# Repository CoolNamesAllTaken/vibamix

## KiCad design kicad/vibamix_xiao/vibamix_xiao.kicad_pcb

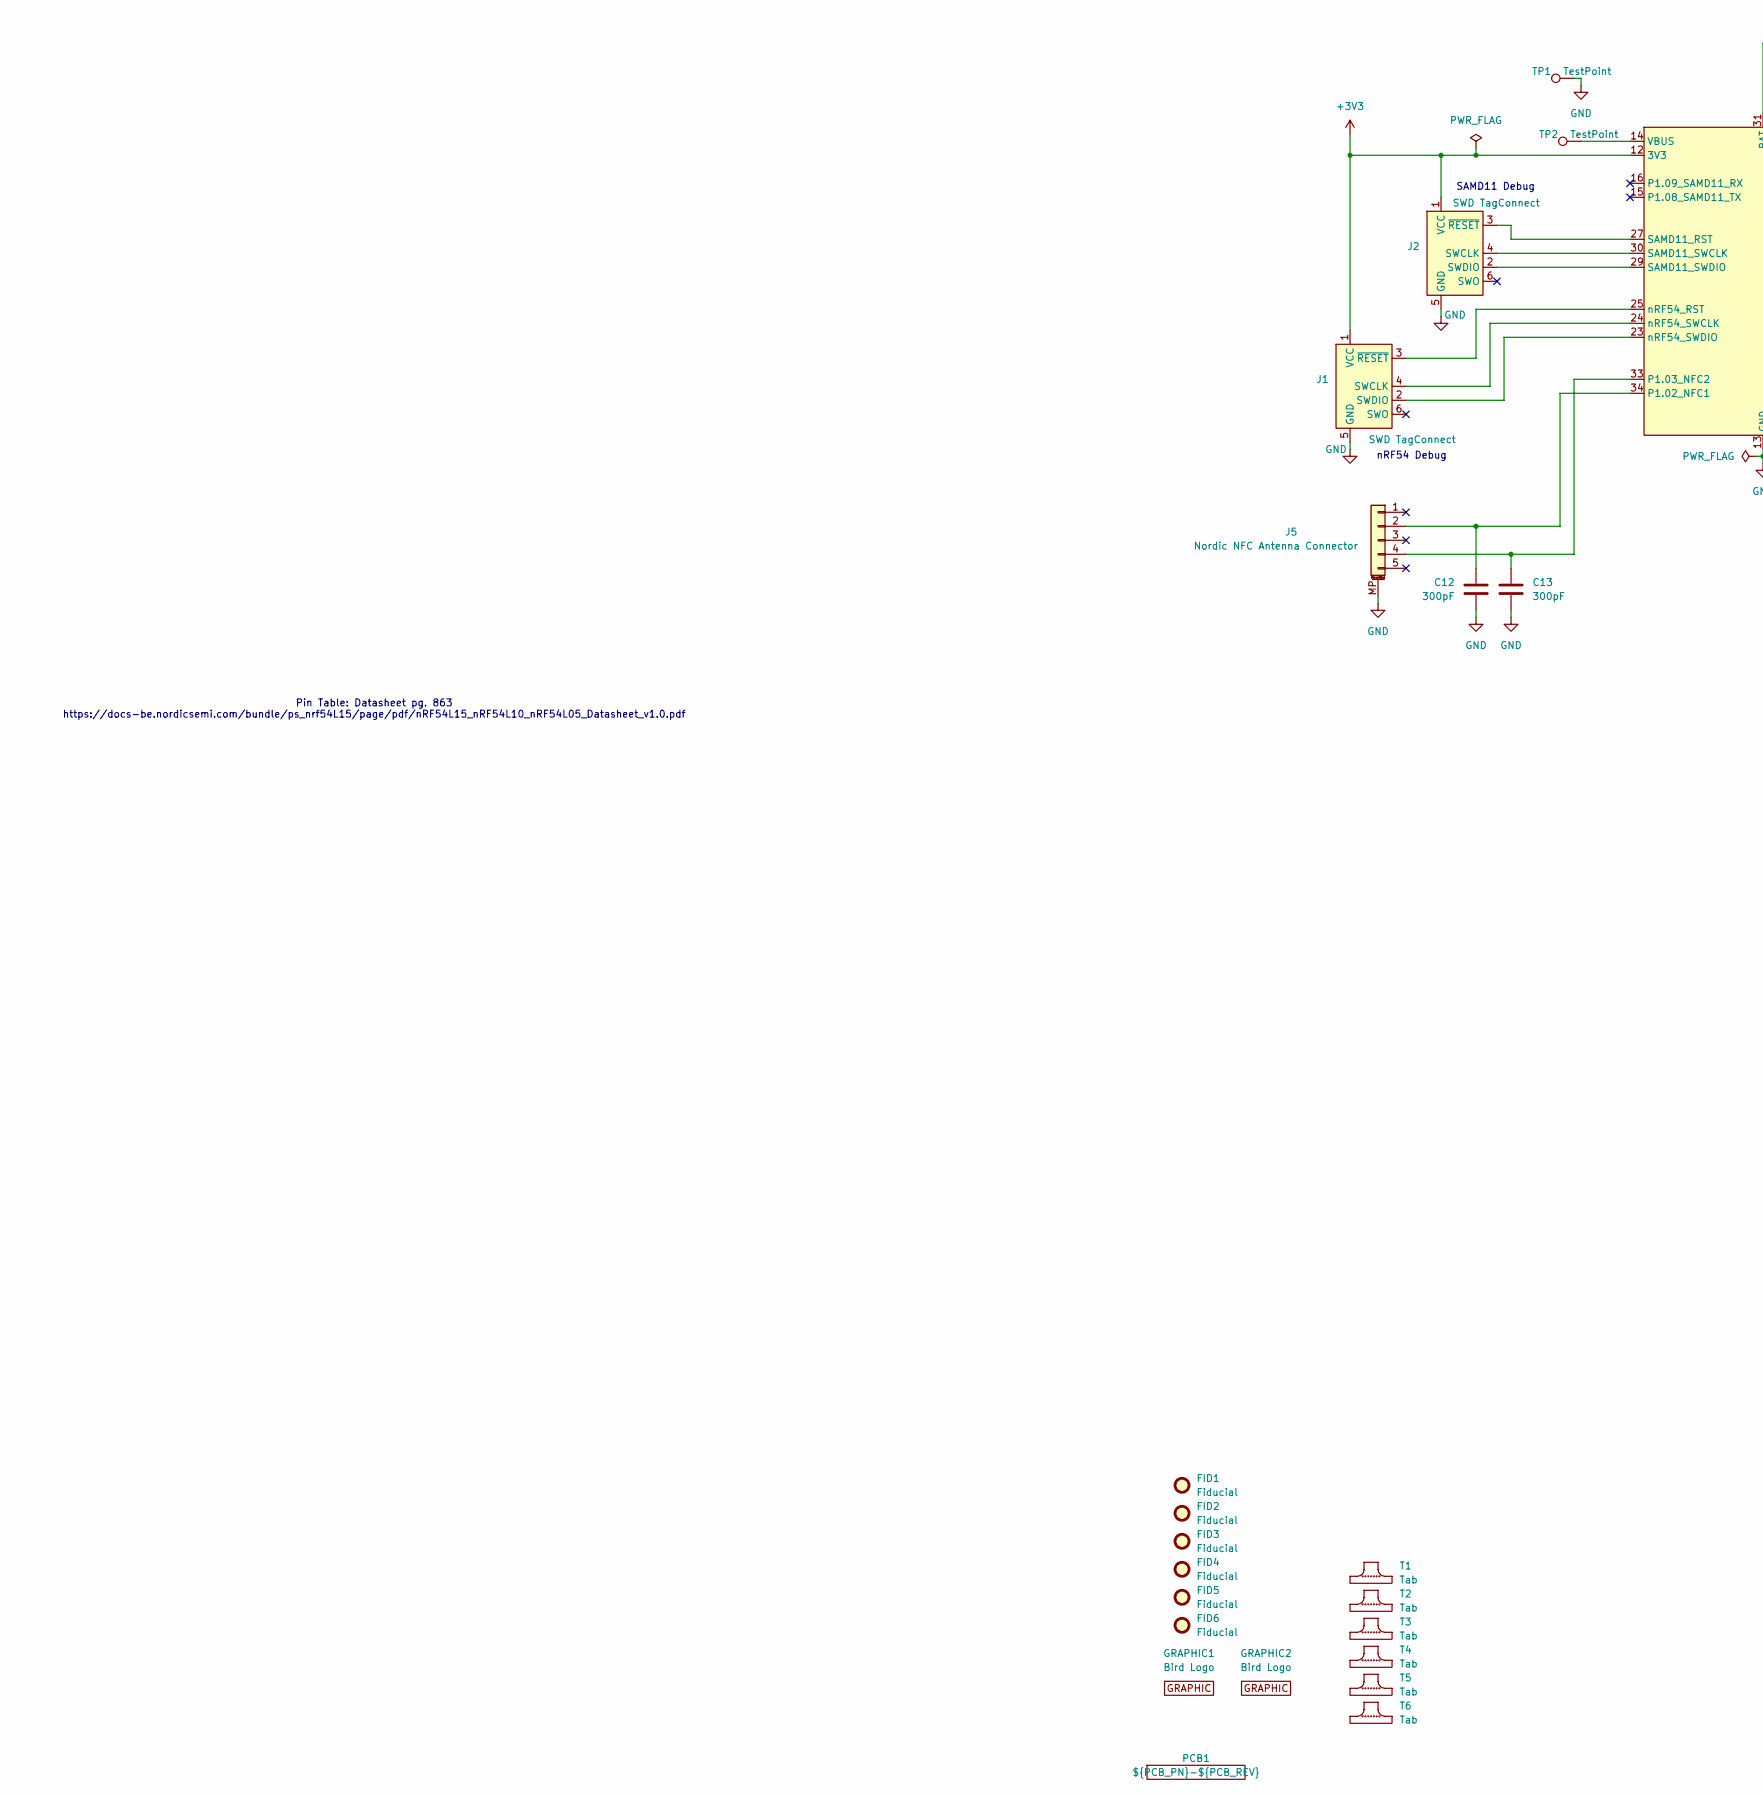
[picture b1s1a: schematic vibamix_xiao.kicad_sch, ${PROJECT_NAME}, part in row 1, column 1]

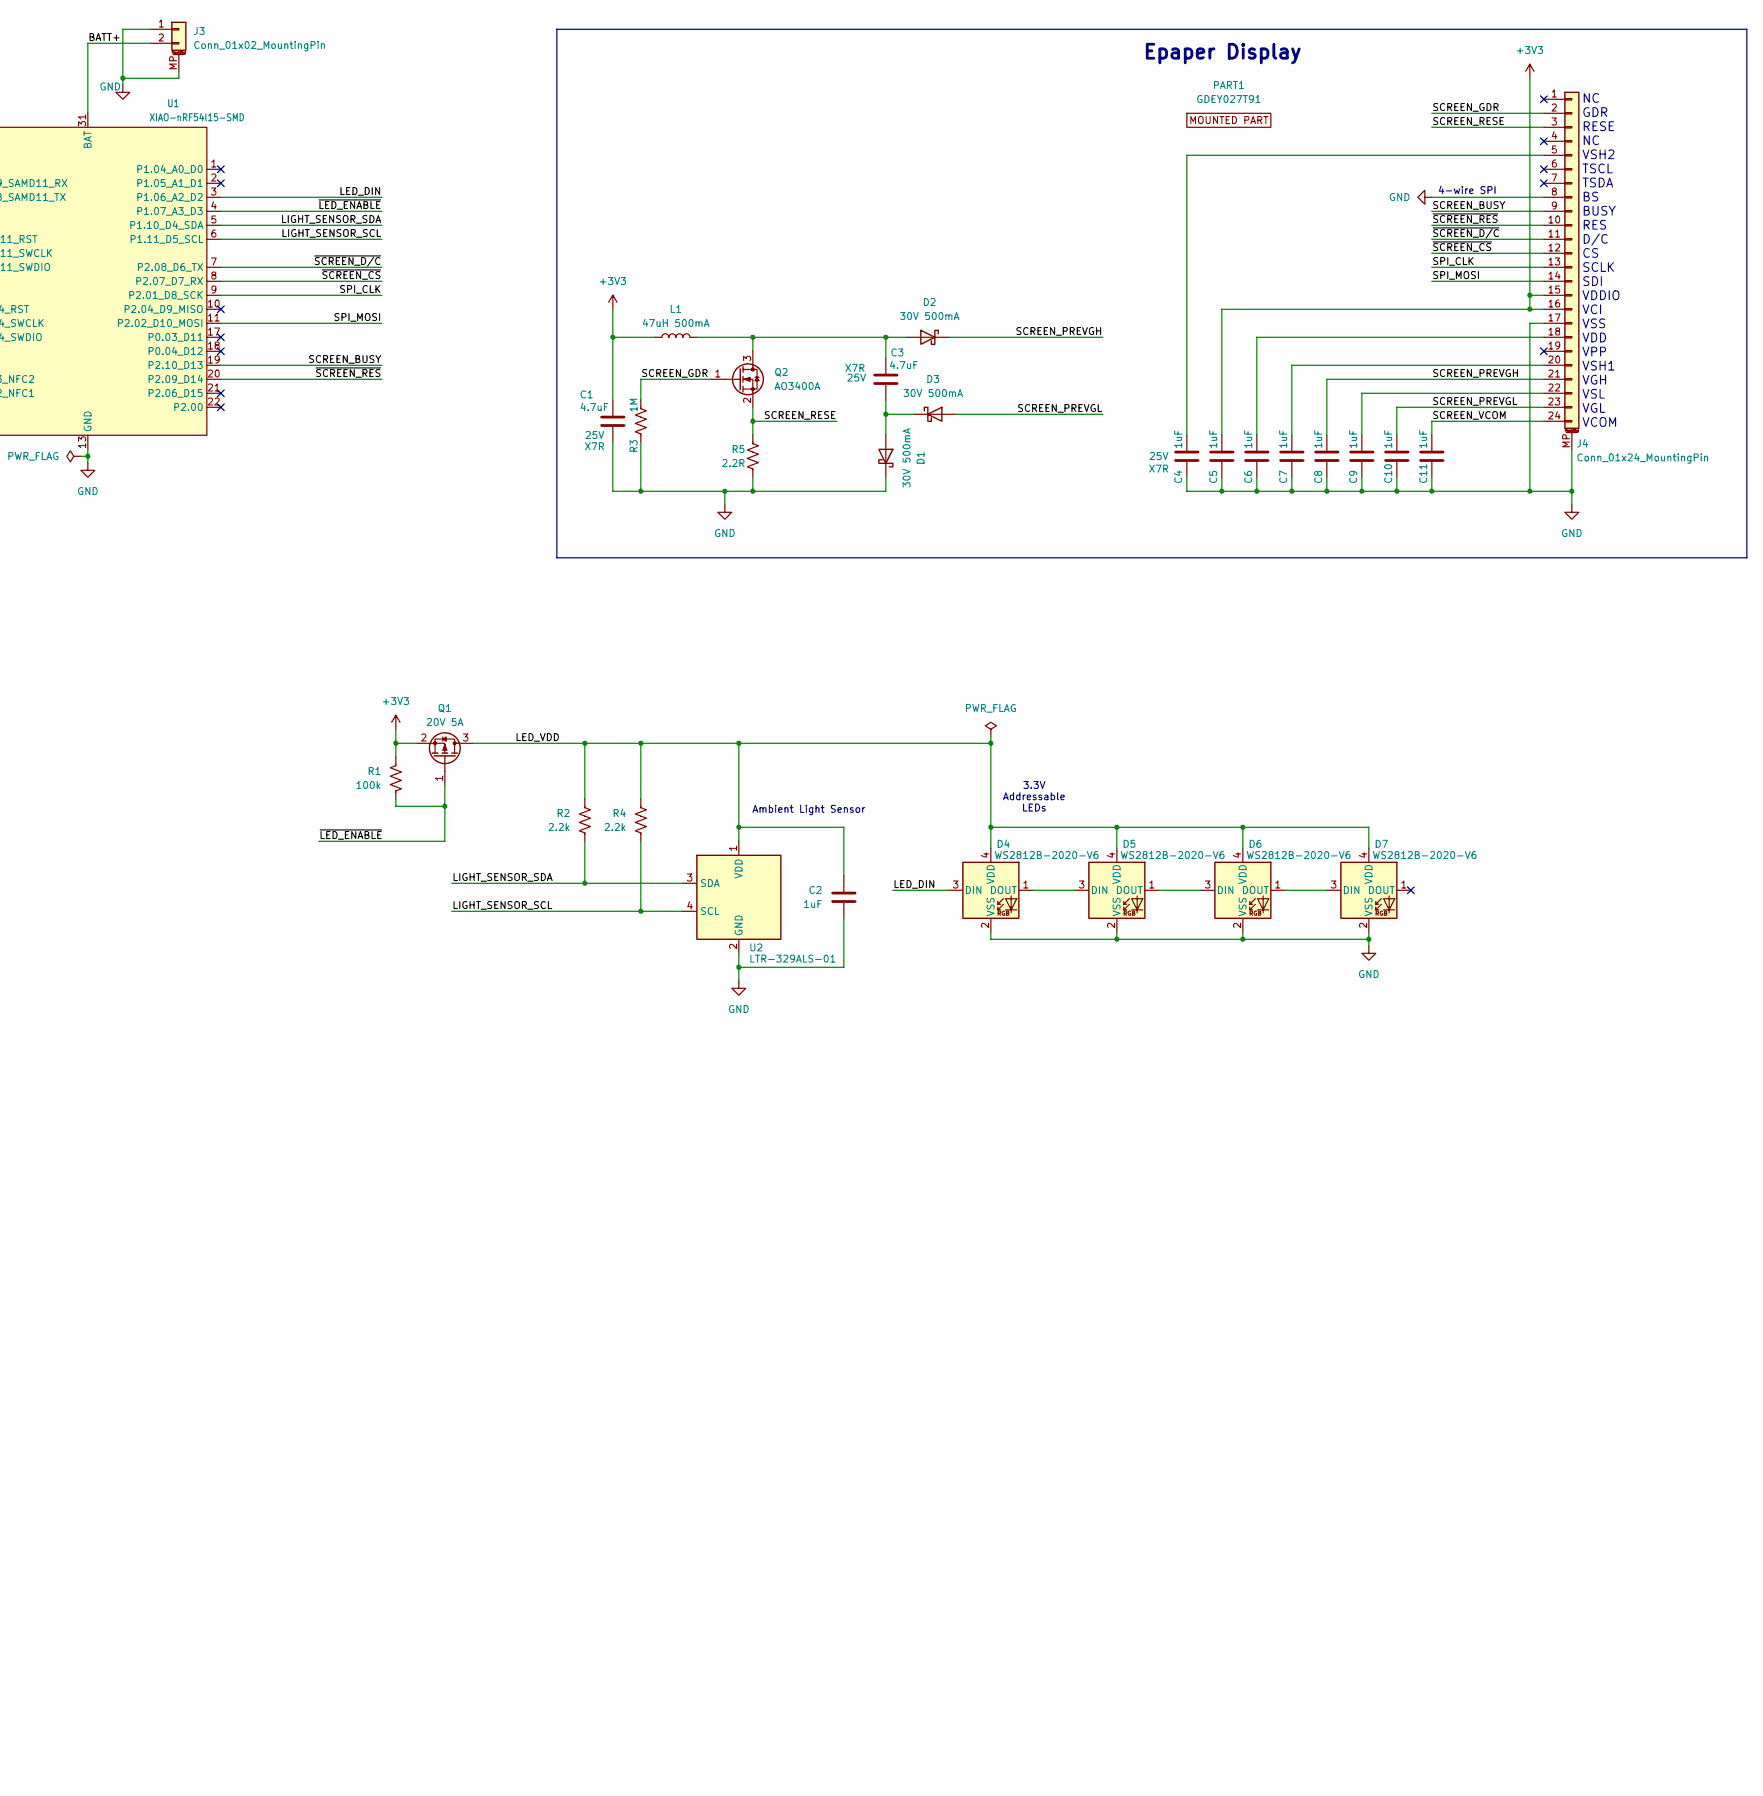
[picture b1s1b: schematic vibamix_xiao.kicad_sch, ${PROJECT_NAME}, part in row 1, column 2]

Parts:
C1, C3: 4.7uF; C_0805_2012Metric; Voltage 25V; Tolerance 10%; MPN CL21B475KAFNNNE; LCSC PN C98195
C2, C4, C5, C6, C7, C8, C9, C10, C11: 1uF; C_0603_1608Metric; Voltage 25V; MPN CL10B105KA8NNNC; LCSC PN C29936
C12, C13: 300pF; C_0402_1005Metric; MPN GRM1555C1H301JA01D
D1, D2, D3: 30V 500mA; D_SOD-123; MPN B0530W-7-F; LCSC PN C124188
D4, D5, D6, D7: WS2812B-2020-V6; LED_WS2812B-2020_PLCC4_2.0x2.0mm; MPN WS2812B-2020-V6; LCSC PN C52917434
FID1, FID2, FID3, FID4, FID5, FID6: Fiducial; Fiducial_0.5mm_Mask1mm_NoCourtyard
GRAPHIC1: Bird Logo; BirdWithPants_Small_Left
GRAPHIC2: Bird Logo; BirdWithPants_Small_Right
J1, J2: SWD TagConnect; Tag-Connect_TC2030-IDC-NL_2x03_P1.27mm_Vertical
J3: Conn_01x02_MountingPin; Molex_PicoBlade_53261-0271_1x02-1MP_P1.25mm_Horizontal; MPN 0532610271
J4: Conn_01x24_MountingPin; Hirose_FH34SRJ-24S-0.5SH_1x24-1MP_P0.50mm_Horizontal_Mirror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; MPN FH34SRJ-24S-0.5SH(50)
J5: Nordic NFC Antenna Connector; FPC-SMD_5P-P0.50_HCTL_HC-FPC-05-10-5RLTAG; MPN HC-FPC-05-10-5RLTAG
L1: 47uH 500mA; L_APV_ANR4012; MPN ANR4012T470M; LCSC PN C7497063
PART1: GDEY027T91; GDEY027T91_NoSlot; MPN GDEY027T91
PCB1: ${PCB_PN}-${PCB_REV}; PCB_PN_REV_Tiny_Silkscreen; MPN ${PCB_PN}
Q1: 20V 5A; SOT-23; MPN DMG2305UX-7
Q2: AO3400A; SOT-23; MPN AO3400A
R1: 100k; R_0402_1005Metric; MPN RC0402FR-07100KL
R2, R4: 2.2k; R_0402_1005Metric; MPN RC0402FR-072K2L
R3: 1M; R_0402_1005Metric; Tolerance 1%; MPN RC0402FR-071ML; LCSC PN C138033
R5: 2.2R; R_0603_1608Metric; Tolerance 1%; MPN RC0603FR-072R2L; LCSC PN C112307
T1, T2, T3, T4, T5, T6: Tab
TP1, TP2: TestPoint; TestPoint_Pad_D1.0mm
U1: XIAO-nRF54l15-SMD; MPN XIAO-nRF54l15-SMD
U2: LTR-329ALS-01; Lite-On_LTR-329ALS-01; MPN LTR-329ALS-01

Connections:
+3V3: C1.2, C5.1, J1.1 (VCC), J2.1 (VCC), J4.15, J4.16, L1.1, Q1.2 (S), R1.1, U1.12 (3V3), U1.28 (3V3)
/BATT+: J3.2, U1.31 (BAT)
/LED_DIN: D4.3 (DIN), U1.3 (P1.06_A2_D2)
/LED_VDD: C2.1, D4.4 (VDD), D5.4 (VDD), D6.4 (VDD), D7.4 (VDD), Q1.3 (D), R2.1, R4.1, U2.1 (VDD)
/LIGHT_SENSOR_SCL: R4.2, U1.6 (P1.11_D5_SCL), U2.4 (SCL)
/LIGHT_SENSOR_SDA: R2.2, U1.5 (P1.10_D4_SDA), U2.3 (SDA)
/SCREEN_BUSY: J4.9, U1.19 (P2.10_D13)
/SCREEN_GDR: J4.2, Q2.1 (G), R3.2
/SCREEN_PREVGH: C8.1, D2.1 (K), J4.21
/SCREEN_PREVGL: C10.1, D3.2 (A), J4.23
/SCREEN_RESE: J4.3, Q2.2 (S), R5.1
/SCREEN_VCOM: C11.1, J4.24
/SPI_CLK: J4.13, U1.9 (P2.01_D8_SCK)
/SPI_MOSI: J4.14, U1.11 (P2.02_D10_MOSI)
/~LED_ENABLE: Q1.1 (G), R1.2, U1.4 (P1.07_A3_D3)
/~SCREEN_CS: J4.12, U1.8 (P2.07_D7_RX)
/~SCREEN_D/C: J4.11, U1.7 (P2.08_D6_TX)
/~SCREEN_RES: J4.10, U1.20 (P2.09_D14)
GND: C1.1, C2.2, C4.2, C5.2, C6.2, C7.2, C8.2, C9.2, C10.2, C11.2, C12.2, C13.2, D1.1 (K), D4.2 (VSS), D5.2 (VSS), D6.2 (VSS), D7.2 (VSS), J1.5 (GND), J2.5 (GND), J3.1, J3.MP (MountPin), J4.8, J4.17, J4.MP (MountPin), J5.MP (MountPin), R3.1, R5.2, TP1.1 (1_1), U1.13 (GND), U1.26 (GND), U1.32 (GND), U2.2 (GND)
unnamed: C3.1, D1.2 (A), D3.1 (K)
unnamed: C3.2, D2.2 (A), L1.2, Q2.3 (D)
unnamed: D4.1 (DOUT), D5.3 (DIN)
unnamed: D5.1 (DOUT), D6.3 (DIN)
unnamed: D6.1 (DOUT), D7.3 (DIN)
unnamed: J1.4 (SWCLK), U1.24 (nRF54_SWCLK)
unnamed: J1.2 (SWDIO), U1.23 (nRF54_SWDIO)
unnamed: J1.3 (~RESET), U1.25 (nRF54_RST)
unnamed: J2.4 (SWCLK), U1.30 (SAMD11_SWCLK)
unnamed: J2.2 (SWDIO), U1.29 (SAMD11_SWDIO)
unnamed: J2.3 (~RESET), U1.27 (SAMD11_RST)
unnamed: C4.1, J4.5
unnamed: C6.1, J4.18
unnamed: C7.1, J4.20
unnamed: C9.1, J4.22
unnamed: C12.1, J5.2, U1.34 (P1.02_NFC1)
unnamed: C13.1, J5.4, U1.33 (P1.03_NFC2)
unnamed: TP2.1 (1_1), U1.14 (VBUS)

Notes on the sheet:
SAMD11 Debug
Ambient Light Sensor
NC GDR RESE NC VSH2 TSCL TSDA BS BUSY RES D/C CS SCLK SDI VDDIO VCI VSS VDD VPP VSH1 VGH VSL VGL VCOM
Pin Table: Datasheet pg. 863 https://docs-be.nordicsemi.com/bundle/ps_nrf54L15/page/pdf/nRF54L15_nRF54L10_nRF54L05_Datasheet_v1.0.pdf
Epaper Display
4-wire SPI
nRF54 Debug
3.3V Addressable LEDs

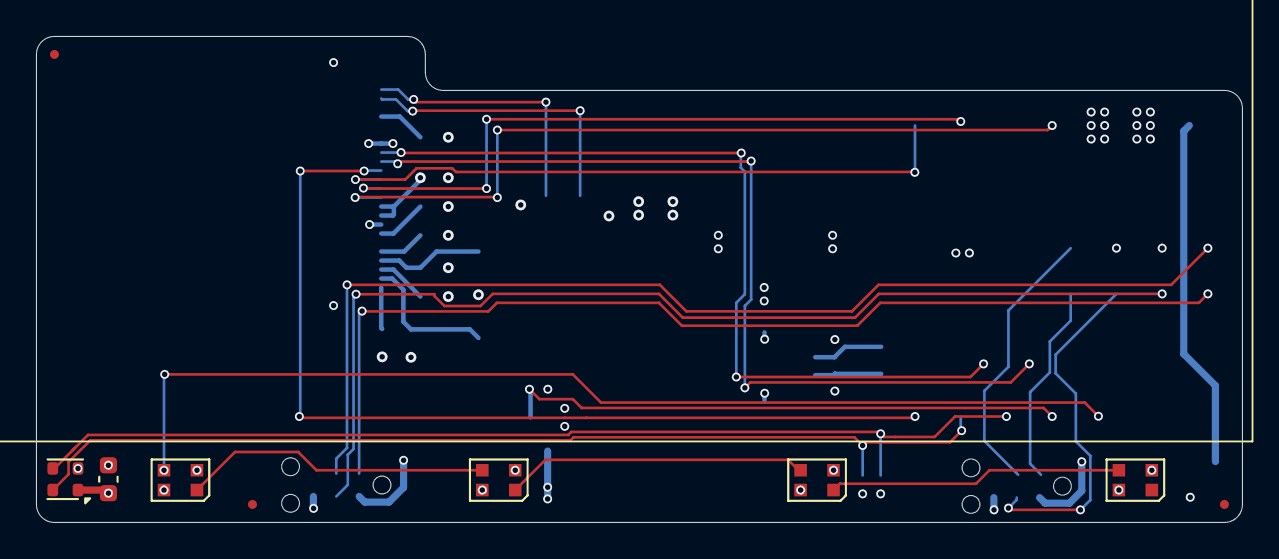
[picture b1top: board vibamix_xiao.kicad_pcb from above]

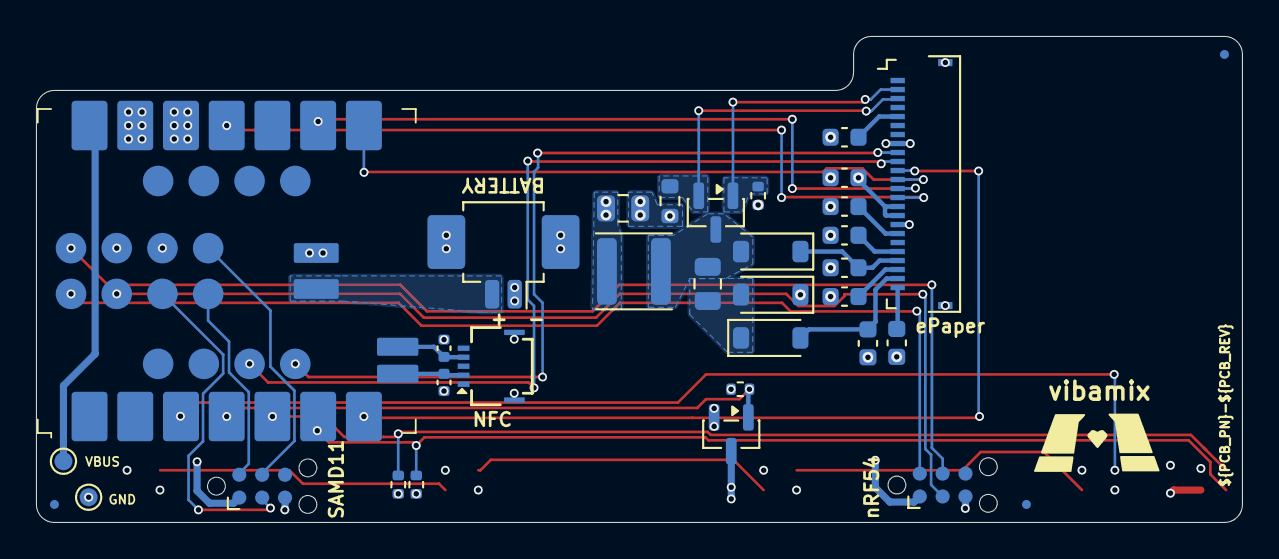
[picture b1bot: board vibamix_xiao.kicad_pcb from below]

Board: 4 copper layers, 67.0 x 27.0 mm, 53 parts (37 on the bottom side), 37 nets.

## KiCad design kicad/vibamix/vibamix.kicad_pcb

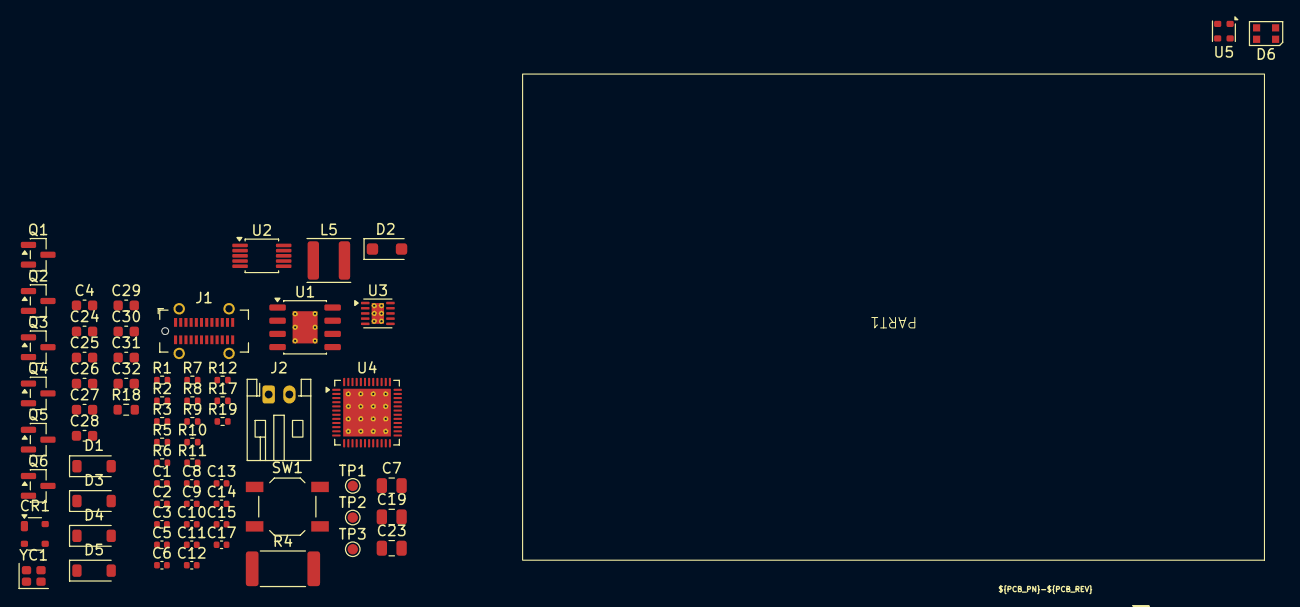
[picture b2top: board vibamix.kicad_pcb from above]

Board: 4 copper layers, 78 parts (1 on the bottom side), 35 nets, no tracks yet.

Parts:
C1, C2, C5, C8, C9, C10, C11, C13: 10uF; C_0402_1005Metric
C3, C6, C12, C14, C15, C17: 0.1uF; C_0402_1005Metric
C4, C24, C25, C26, C27, C28, C29, C30, C31, C32: 1uF; C_0603_1608Metric
C7: 10uF; C_0805_2012Metric
C19, C23: 4.7uF; C_0805_2012Metric
CR1: DRTR5V0U2SR-7; SOT-143
D1: 1N4148; D_SOD-123
D2: 40V 2A; D_SOD-123F
D3, D4, D5: 30V 500mA; D_SOD-123
D6: WS2812B-2020-V6; LED_WS2812B-2020_PLCC4_2.0x2.0mm
GRAPHIC1: Bird Logo; BirdWithPants_Small_Left
H1, H2: M2.5 Mounting Hole; MountingHole_2.7mm_M2.5_Isolated
J1: USB_C_Receptacle_USB2.0; USB_C_Receptacle_GCT_USB4115-03-C
J2: JST-PH 01x02 Male; JST_PH_S2B-PH-K_1x02_P2.00mm_Horizontal
J4: Conn_01x24_MountingPin; Hirose_FH34SRJ-24S-0.5SH_1x24-1MP_P0.50mm_Horizontal_Mirror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
L5: 47uH 500mA; L_APV_ANR4012
PART1: GDEY027T91; GDEY027T91-FL02
PCB1: PCB_PN-A; PCB_PN_REV_Tiny_Silkscreen
Q1, Q3, Q5: AO3400A; SOT-23
Q2, Q4, Q6: 20V 4.2A; SOT-23
R1, R2, R6: 5.1k 1%; R_0402_1005Metric
R3, R5, R10: 10k; R_0402_1005Metric
R4: 0.47R 1% 1W; R_2512_6332Metric
R7, R8, R9, R11, R12, R19: 100k; R_0402_1005Metric
R17: 1M; R_0402_1005Metric
R18: 2.2R; R_0603_1608Metric
SW1: SW_Push; SW_SPST_TL3342
T1, T2, T3, T4: Tab
TP1, TP2, TP3: TestPoint; TestPoint_Pad_D1.0mm
U1: TP4056; HSOP-8-1EP_3.9x4.9mm_P1.27mm_EP2.41x3.1mm_ThermalVias
U2: CH340E; MSOP-10_3x3mm_P0.5mm
U3: TPS63900; WSON-10-1EP_2.5x2.5mm_P0.5mm_EP1.2x2mm_ThermalVias
U4: nRF54L15-QDXX; QFN-48-1EP_6x6mm_P0.4mm_EP4.6x4.6mm_ThermalVias
U5: LTR-329ALS-01; Lite-On_LTR-329ALS-01
YC1: 32MHz; Crystal_SMD_2016-4Pin_2.0x1.6mm

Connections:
+BATT: C5.1, J2.2, Q2.2 (S), R5.1, R7.1, U1.5 (BAT)
/DECA: U4.33 (DECRF), U4.43 (DECA)
/LED_ENABLE: Q6.1 (G), R19.2
/LED_VDD: C29.1, D6.4 (VDD), Q6.3 (D), U5.1 (VDD)
/POHO_CTRL: Q1.1 (G), R3.1
/POHO_OUT: C7.1, Q2.3 (D), Q4.3 (D), R9.1
/REG_IN: C8.1, D2.1 (K), Q4.2 (S), U3.1 (EN), U3.10 (VIN)
/SCREEN_GDR: J4.2, Q5.1 (G), R17.2
/SCREEN_PREVGH: C28.1, D4.1 (K), J4.21, TP1.1 (1_1)
/SCREEN_PREVGL: C31.1, D5.2 (A), J4.23, TP2.1 (1_1)
/SCREEN_RESE: J4.3, Q5.2 (S), R18.1
/SCREEN_VCOM: C32.1, J4.24, TP3.1 (1_1)
/VDD_VOLTAGE_SELECT: R11.2, R12.1, U3.2 (SEL)
GND: C1.2, C2.2, C3.1, C5.2, C6.1, C8.2, C9.2, C10.2, C11.2, C12.1, C13.2, C14.1, C15.1, C17.1, C19.1, C24.2, C25.2, C26.2, C27.2, C28.2, C29.2, C30.2, C31.2, C32.2, CR1.1 (GND), D3.1 (K), D6.2 (VSS), J1.A1 (GND), J1.A12 (GND), J1.B1 (GND), J1.B12 (GND), J2.1, J4.8, J4.17, J4.MP (MountPin), Q1.2 (S), Q3.2 (S), R1.2, R2.2, R3.2, R6.2, R10.2, R12.2, R17.1, R18.2, SW1.1, U1.3 (GND), U1.9 (GND), U2.3 (GND), U3.8 (GND), U3.11 (GND), U4.32 (VSS_PA), U4.44 (VSS), U4.49 (VSS), U5.2 (GND), YC1.2 (G), YC1.4 (G)
unnamed: CR1.2 (IO1), J1.A6 (D+), J1.B6 (D+), U2.1 (UD+)
unnamed: CR1.3 (IO2), J1.A7 (D-), J1.B7 (D-), U2.2 (UD-)
unnamed: D1.2 (A), R8.2, R9.2
unnamed: C4.1, D1.1 (K), Q1.3 (D), R5.2, SW1.2
unnamed: C23.1, D3.2 (A), D5.1 (K)
unnamed: C23.2, D4.2 (A), L5.2, Q5.3 (D)
unnamed: J1.A5 (CC1), R1.1
unnamed: J1.B5 (CC2), R2.1
unnamed: C24.1, J4.5
unnamed: C26.1, J4.18
unnamed: C27.1, J4.20
unnamed: C30.1, J4.22
unnamed: C4.2, Q2.1 (G), Q3.3 (D), R7.2
unnamed: C7.2, Q3.1 (G), R8.1
unnamed: C1.1, R4.2, U1.4 (Vcc), U1.8 (CE)
unnamed: R6.1, U1.2 (PROG)
unnamed: C6.2, U2.10 (V3)
unnamed: U4.34 (XC1), YC1.1
unnamed: U4.35 (XC2), YC1.3
VBUS: C2.1, C3.2, CR1.4 (Vcc), D2.2 (A), J1.A4 (VBUS), J1.A9 (VBUS), J1.B4 (VBUS), J1.B9 (VBUS), Q4.1 (G), R4.1, R10.1, U2.7 (VCC)
VDD: C9.1, C10.1, C11.1, C12.2, C13.1, C14.2, C15.2, C17.2, C19.2, C25.1, J4.15, J4.16, L5.1, Q6.2 (S), R11.1, R19.1, U3.6 (VOUT), U4.10 (VDD), U4.22 (VDD), U4.36 (VDD), U4.47 (VDD), U4.48 (VDD)

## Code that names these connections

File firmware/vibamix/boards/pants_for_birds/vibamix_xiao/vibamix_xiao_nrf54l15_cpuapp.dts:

/dts-v1/;

#include <nordic/nrf54l15_cpuapp.dtsi>
#include "vibamix_xiao-pinctrl.dtsi"
#include <zephyr/dt-bindings/led/led.h>

/ {
	model = "Xiao NRF54L15 ePaper badge.";
	compatible = "pants_for_birds,vibamix-xiao-cpuapp";

	chosen {
		zephyr,code-partition = &slot0_partition;
		zephyr,sram = &cpuapp_sram;
		zephyr,flash = &cpuapp_rram;
		zephyr,flash-controller = &rram_controller;
	};

	/* LED strip power enable - active low */
	leds {
		compatible = "gpio-leds";
		led_enable: led_enable {
			gpios = <&gpio1 7 GPIO_ACTIVE_LOW>;	/* P1.07 LED_ENABLE */
		};
	};

	aliases {
		led-strip = &led_strip;
		epaper    = &epaper;
	};
};

/* ePaper display on SPI20 */
&spi20 {
	compatible = "nordic,nrf-spim";
	status = "okay";
	pinctrl-0 = <&spi20_default>;
	pinctrl-1 = <&spi20_sleep>;
	pinctrl-names = "default", "sleep";
	cs-gpios = <&gpio2 7 GPIO_ACTIVE_LOW>;		/* P2.07 SCREEN_CS  */

	epaper: epaper@0 {
		compatible = "solomon,ssd1680";		/* update to match your controller */
		reg = <0>;
		spi-max-frequency = <4000000>;
		width = <250>;
		height = <122>;
		dc-gpios   = <&gpio2 8 GPIO_ACTIVE_LOW>;	/* P2.08 SCREEN_D/C  */
		reset-gpios = <&gpio2 9 GPIO_ACTIVE_LOW>;	/* P2.09 SCREEN_RES  */
		busy-gpios  = <&gpio2 10 GPIO_ACTIVE_HIGH>;	/* P2.10 SCREEN_BUSY */
	};
};

/* WS2812 LED strip on SPI21 - only MOSI (P1.06) is physically connected */
&spi21 {
	compatible = "nordic,nrf-spim";
	status = "okay";
	pinctrl-0 = <&spi21_default>;
	pinctrl-1 = <&spi21_sleep>;
	pinctrl-names = "default", "sleep";

	led_strip: ws2812@0 {
		compatible = "worldsemi,ws2812-spi";
		reg = <0>;
		spi-max-frequency = <DT_FREQ_M(8)>;
		chain-length = <1>;			/* update to your actual LED count */
		color-mapping = <LED_COLOR_ID_GREEN
				 LED_COLOR_ID_RED
				 LED_COLOR_ID_BLUE>;
		spi-one-frame  = <0x70>;
		spi-zero-frame = <0x40>;
	};
};

/* Light sensor I2C bus */
&i2c20 {
	compatible = "nordic,nrf-twim";
	status = "okay";
	pinctrl-0 = <&i2c20_default>;
	pinctrl-1 = <&i2c20_sleep>;
	pinctrl-names = "default", "sleep";
	/* add sensor child node here once you know the I2C address and compatible */
};

&grtc {
	owned-channels = <0 1 2 3 4 5 6 7 8 9 10 11>;
	/* Channels 7-11 reserved for Zero Latency IRQs, 3-4 for FLPR */
	child-owned-channels = <3 4 7 8 9 10 11>;
	status = "okay";
};

&cpuapp_sram {
	status = "okay";
};

&cpuapp_rram {
	partitions {
		compatible = "fixed-partitions";
		#address-cells = <1>;
		#size-cells = <1>;

		boot_partition: partition@0 {
			label = "mcuboot";
			reg = <0x0 DT_SIZE_K(64)>;
		};

		slot0_partition: partition@10000 {
			label = "image-0";
			reg = <0x10000 DT_SIZE_K(664)>;
		};

		slot1_partition: partition@b6000 {
			label = "image-1";
			reg = <0xb6000 DT_SIZE_K(664)>;
		};

		storage_partition: partition@15c000 {
			label = "storage";
			reg = <0x15c000 DT_SIZE_K(36)>;
		};
	};
};

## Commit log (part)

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2026-05-06 PCBA Rev A
2026-05-13 Add NRF application with ePaper driver migrated to Zephyr
2026-05-14 OpenOCD debugging and serial console on vibamix_zephyr
2026-05-14 ePaper hello world!
2026-05-24 Save progress
2026-06-11 update gitignore
2026-06-11 add build and flash to app
2026-06-12 Adds Python App for Flashing Multiple Devices (#1)
    * Save progress
    * Save progress
    * Initial Commit
    * update gitignore
    * Update README.md
    * add build and flash to app
2026-06-12 Adds support for ALS
2026-06-14 Add agents file
2026-06-14 Commit enclosure stuff
2026-06-14 Sync vibamix firmware with main
2026-06-14 Add uncommitted changes
2026-06-14 Remove baremetal vibamix directory
2026-06-15 Add LED animation, swith to BLE mesh, update debug config
2026-06-15 Get LEDs working
2026-06-16 Add variable width font system and improve screen behavior
2026-06-16 John/bringup (#3)
    * Add agents file
    * Commit enclosure stuff
    * Add uncommitted changes
    * Sync vibamix firmware with main
    * Remove baremetal vibamix directory
    * Add LED animation, swith to BLE mesh, update debug config
2026-06-16 Work on BLE application
2026-06-16 Add LEDs to diagnostic bringup
2026-06-16 Clean up code
2026-06-16 Clean up ALS driver
2026-06-17 WIP adding OTA
2026-06-17 Bootloader working!
2026-06-17 Package OTA files
2026-06-17 Fix contrast dying on partial refresh
2026-06-18 Fix OTA updates
2026-06-18 Add CLAUDE file and badge mascots
2026-06-18 Save progress before mesh change
2026-06-18 Remove GATT proxy
2026-06-18 Improve LED animations and fix display shift
2026-06-18 Fix ghosting issue
2026-06-18 Fix pixel shift
2026-06-18 Make disconnect behavior go to sleep countdown
2026-06-18 Abandon grayscale in place
2026-06-18 Add sleep mode and stuff
2026-06-18 Maybe fix some OTA stuff
2026-06-18 Get mesh working
2026-06-18 Extend flashtool with programming capability
2026-06-19 Add commit hash to diagnostic screen
2026-06-19 Fix ESD diode leakage current
2026-06-19 5mA sleep
2026-06-19 WIP battery lockup debug
2026-06-19 Heck yeah
2026-06-20 Change auto brightness adjustment thresholds on LEDs
2026-06-20 Make config screen the default, add OTA loading bar to ePaper, add brightness control mesh command, add rainbow sparkle LED animation, make badgectl adaptive height, add party mode button to badgectl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
2026-06-20 Prune stale devices, update placard design
2026-06-20 Add bulk programming
2026-06-20 Ready to go
